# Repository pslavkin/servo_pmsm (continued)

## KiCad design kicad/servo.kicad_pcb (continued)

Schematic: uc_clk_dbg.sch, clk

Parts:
C601: 1nF; C_0603_1608Metric
C602: 0.01uF; C_0603_1608Metric
C603: 0.1uF; C_0603_1608Metric
D603: green; LED_0603_1608Metric
D604: blue; LED_0603_1608Metric
J601: dbg_conn; PinSocket_2x06_P2.54mm_Vertical
R603, R606: 1.0k; R_0603_1608Metric
R604, R605: 56k; R_0805_2012Metric_Pad1.15x1.40mm_HandSolder
R607, R610: 2.2k; R_0603_1608Metric
R608, R609: 680; R_0603_1608Metric
U301: TMS320F28388DZWTS; BGA337CP80_19X19_1600X1600X140B50N; PartNumber TMS320F28388DZWTS
U601: SN74ALVC244PW; TSSOP-20_4.4x6.5mm_P0.65mm
U602: M25PX32-VMW; SOIJ-8_5.3x5.3mm_P1.27mm
Y601: Oscillator_SMD_SeikoEpson_SG210-4Pin_2.5x2.0mm

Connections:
3V3: C603.2 (Capacitor), D603.2 (A), D604.2 (A), J601.2, R604.1, R605.1, R610.2, U601.1 (1~OE), U601.19 (2~OE), U601.20 (VCC), U602.3 (W#/VPP), U602.7 (HOLD#), U602.8 (VCC), Y601.1 (TRI-STATE), Y601.4 (VCC); also elsewhere on the board
5VC: J601.1; also elsewhere on the board
/uc_clk_dbg/F2838x_CLK: U301.G19 (X1), Y601.3 (OUTPUT)
/uc_clk_dbg/MCU_TCK: U301.V15 (TCK), U601.18 (1Y1)
/uc_clk_dbg/MCU_TDI: U301.W13 (TDI), U601.16 (1Y2)
/uc_clk_dbg/MCU_TDO: U301.W15 (TDO), U601.11 (2A1)
/uc_clk_dbg/MCU_TMS: U301.W14 (TMS), U601.14 (1Y3)
/uc_clk_dbg/MCU_TRSTn: R607.2, U301.V14 (TRST), U601.12 (1Y4)
/uc_clk_dbg/MCU_XRSn: C602.1, R610.1, U301.F19 (XRS)
/uc_clk_dbg/PRG_SCI_RX: J601.4, R603.2, U601.5 (2Y3)
/uc_clk_dbg/PRG_SCI_TX: J601.3, U601.17 (2A4)
/uc_clk_dbg/PRG_TCK: J601.12, U601.2 (1A1)
/uc_clk_dbg/PRG_TDI: J601.11, U601.4 (1A2)
/uc_clk_dbg/PRG_TDO: J601.8, U601.9 (2Y1)
/uc_clk_dbg/PRG_TMS: J601.10, U601.6 (1A3)
/uc_clk_dbg/PRG_TRSTn: J601.9, U601.8 (1A4)
BOOT1: R604.2; also elsewhere on the board
BOOT2: R605.2; also elsewhere on the board
DACB_DBG: R608.1; also elsewhere on the board
DACB_DBG_OUT: J601.7, R609.2
FLASH_SPI_CLK: U602.6 (C); also elsewhere on the board
FLASH_SPI_CS: U602.1 (S#); also elsewhere on the board
FLASH_SPI_MISO: U602.2 (DQ1); also elsewhere on the board
FLASH_SPI_MOSI: U602.5 (DQ0); also elsewhere on the board
GND: C601.1, C602.2 (Capacitor), C603.1, J601.5, J601.6, R607.1, U601.10 (GND), U601.13 (2A2), U602.4 (VSS), Y601.2 (GND); also elsewhere on the board
unnamed: C601.2 (Capacitor), R608.2, R609.1
unnamed: D603.1 (K), R603.1
unnamed: D604.1 (K), R606.1
SCIA_RX: R606.2, U601.3 (2Y4); also elsewhere on the board
SCIA_TX: U601.15 (2A3); also elsewhere on the board

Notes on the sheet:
I left fixed in flash mode if you need to change it you'll get dirty
25MHz Clock
Reset
SPI FLASH
To store some firmware features, and maybe UI images or screens
ADC/DAC DBG OUT
it's just optional for debug porpouses to monitor some analog signal out from the board, it could be very handy
Programmer connector plus SCI for debug porpouses.. take in account that it's not isolated, only buffered to minimize risk. It's supoussed that th 3v3 cold side never touch 220v
CLK + JTAG + SCI
BOOTSRAP R's

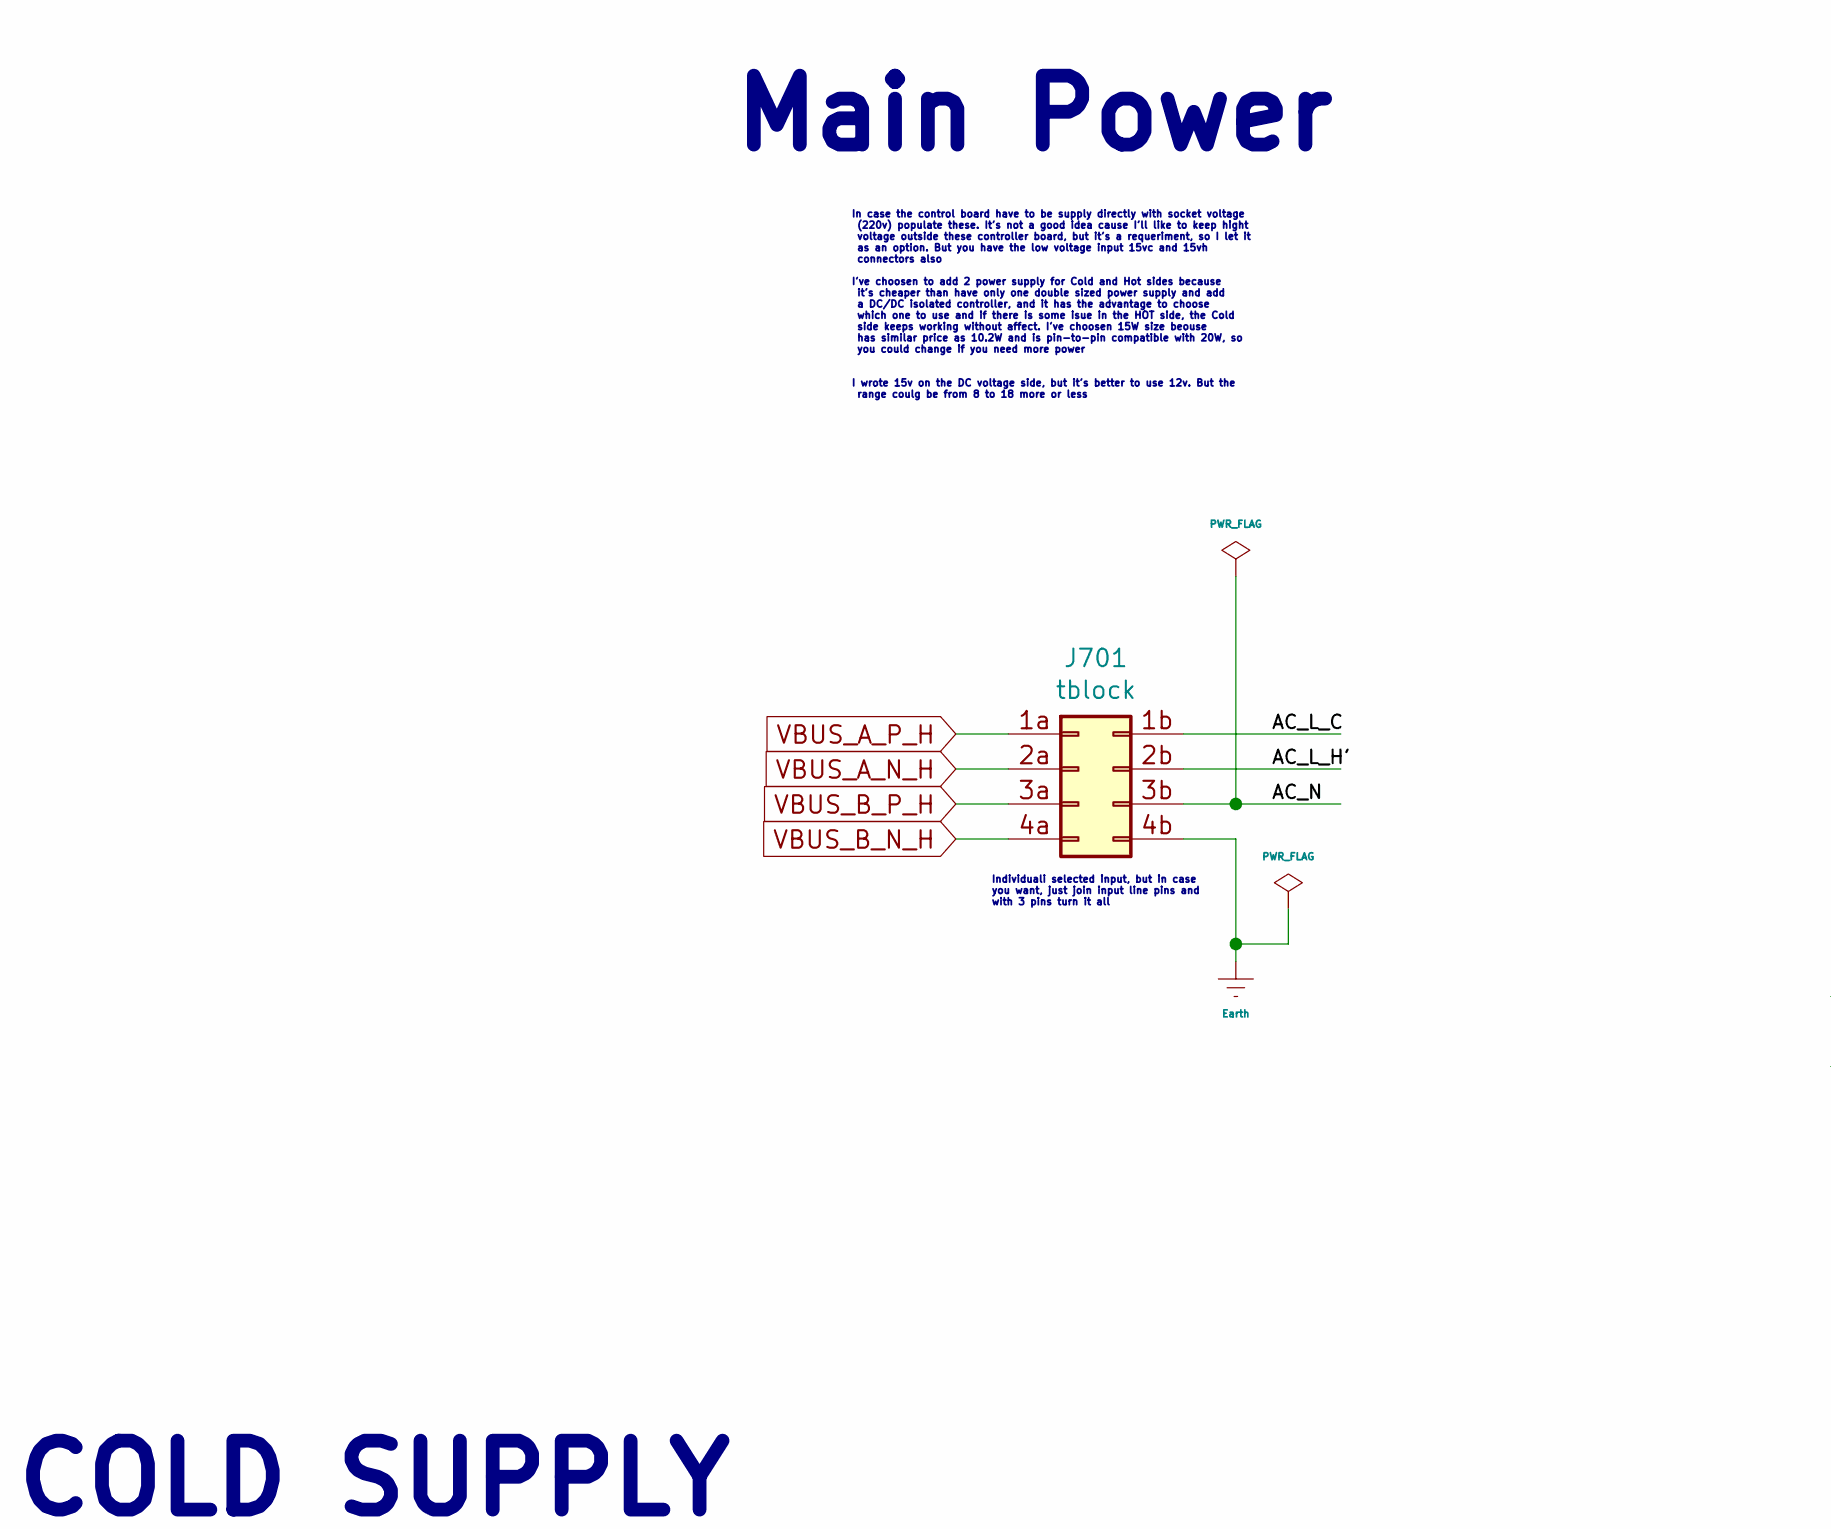
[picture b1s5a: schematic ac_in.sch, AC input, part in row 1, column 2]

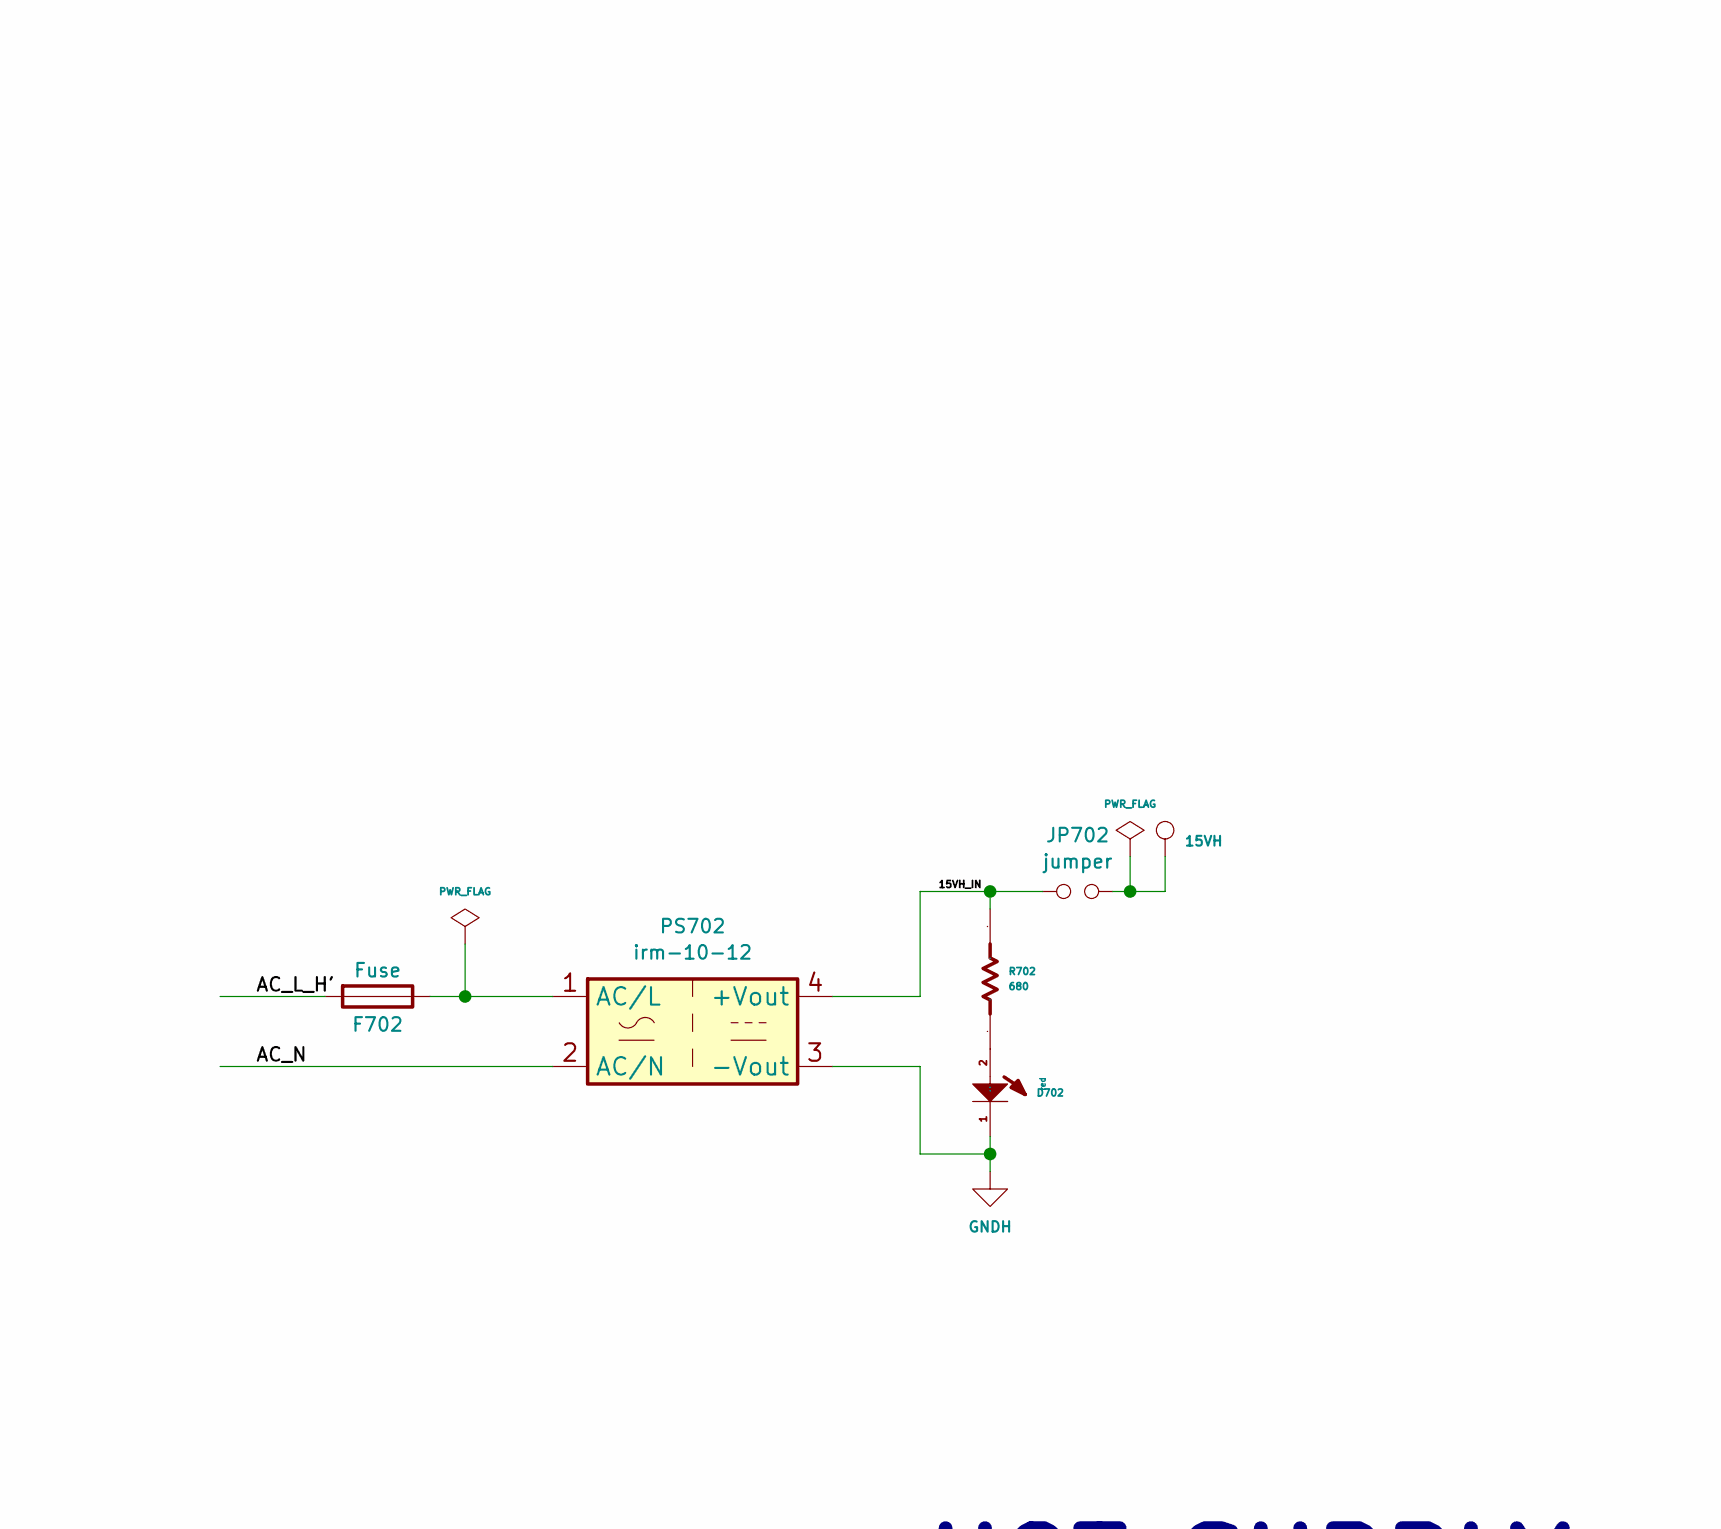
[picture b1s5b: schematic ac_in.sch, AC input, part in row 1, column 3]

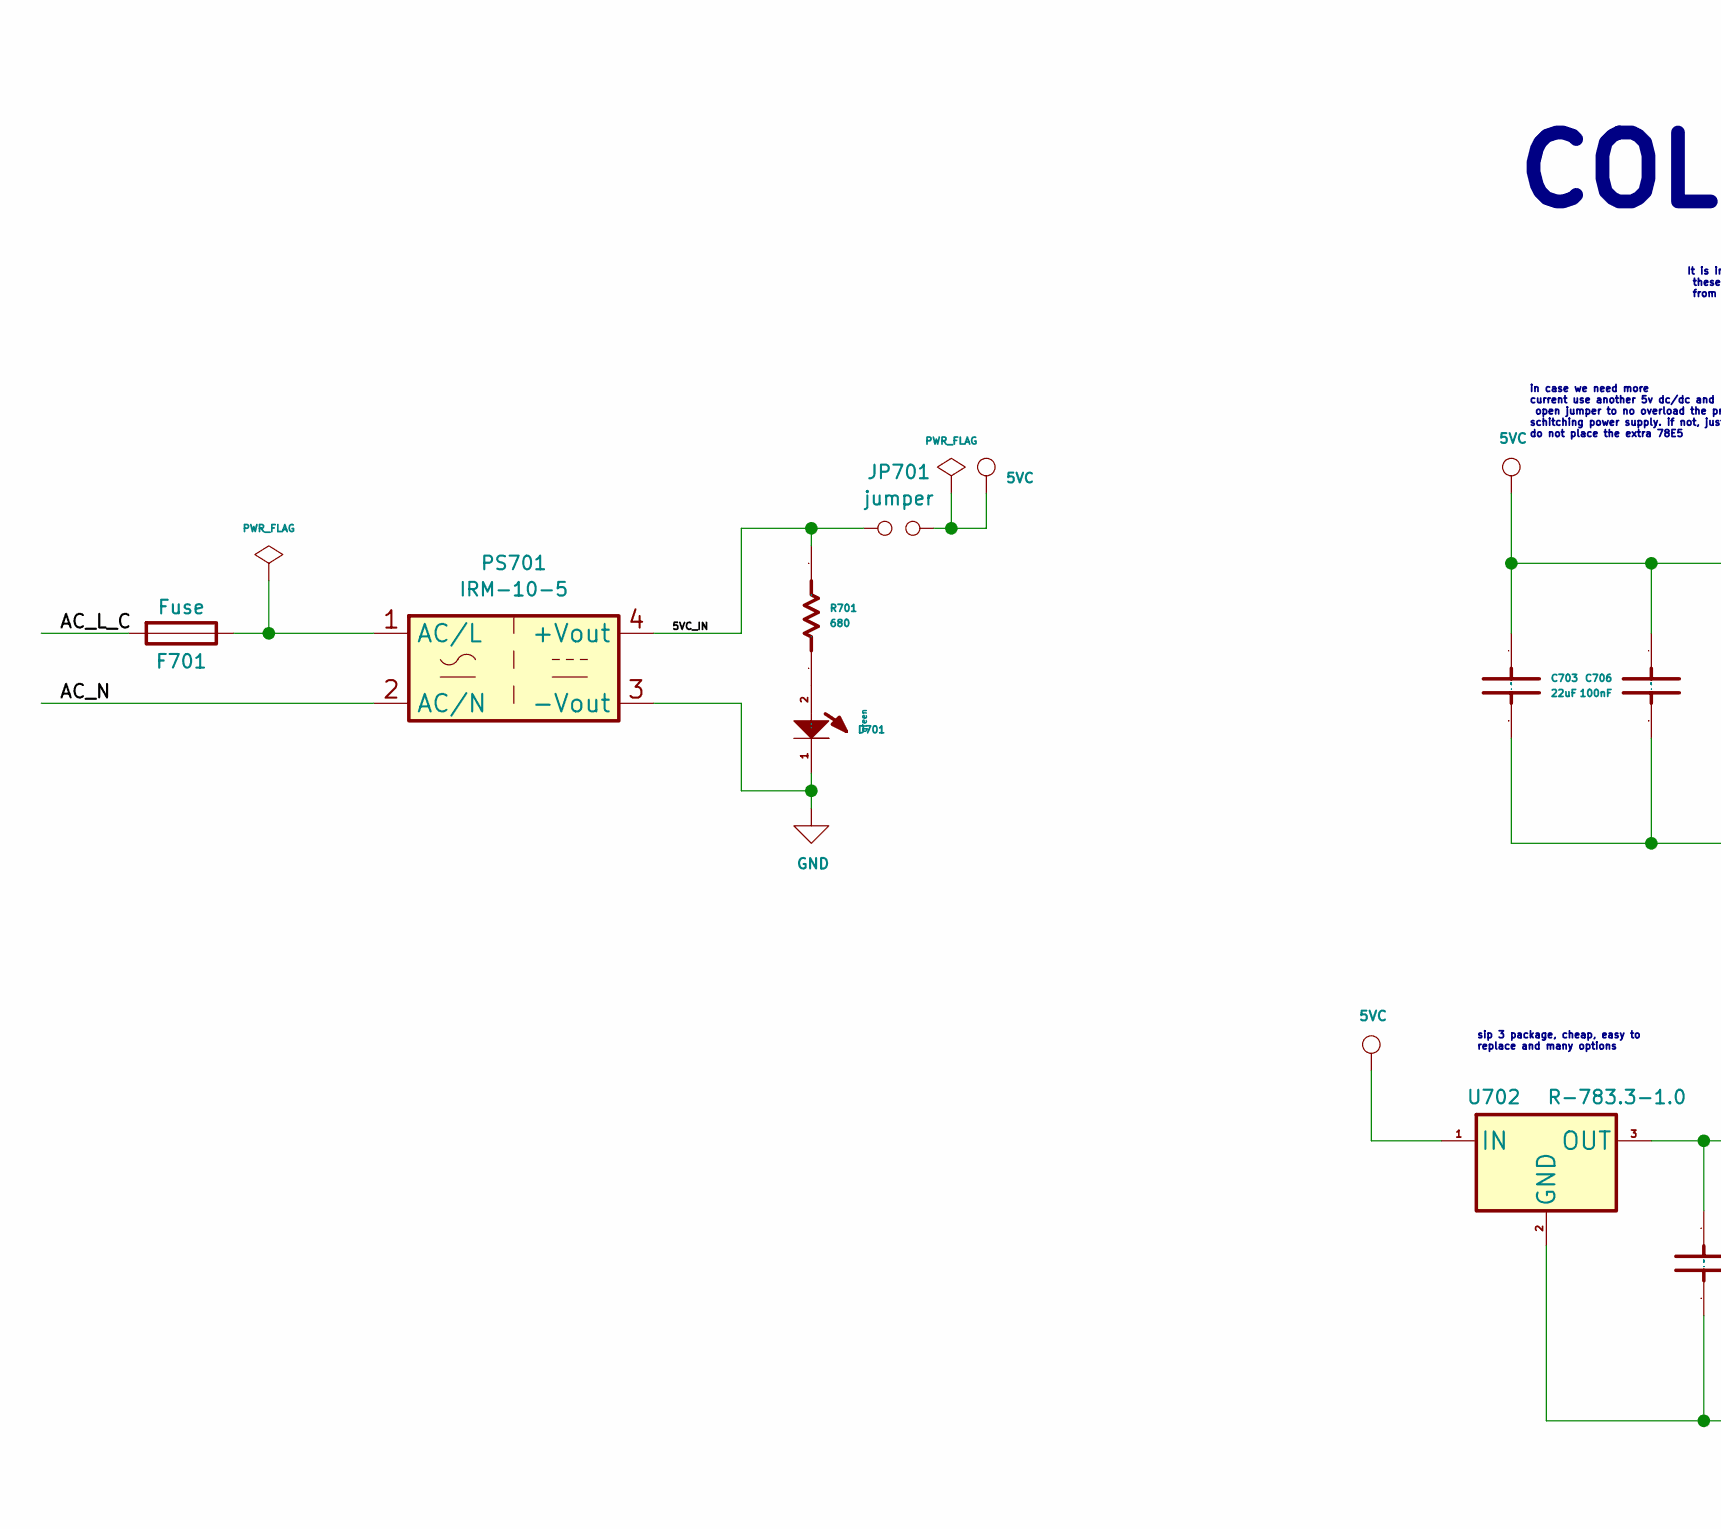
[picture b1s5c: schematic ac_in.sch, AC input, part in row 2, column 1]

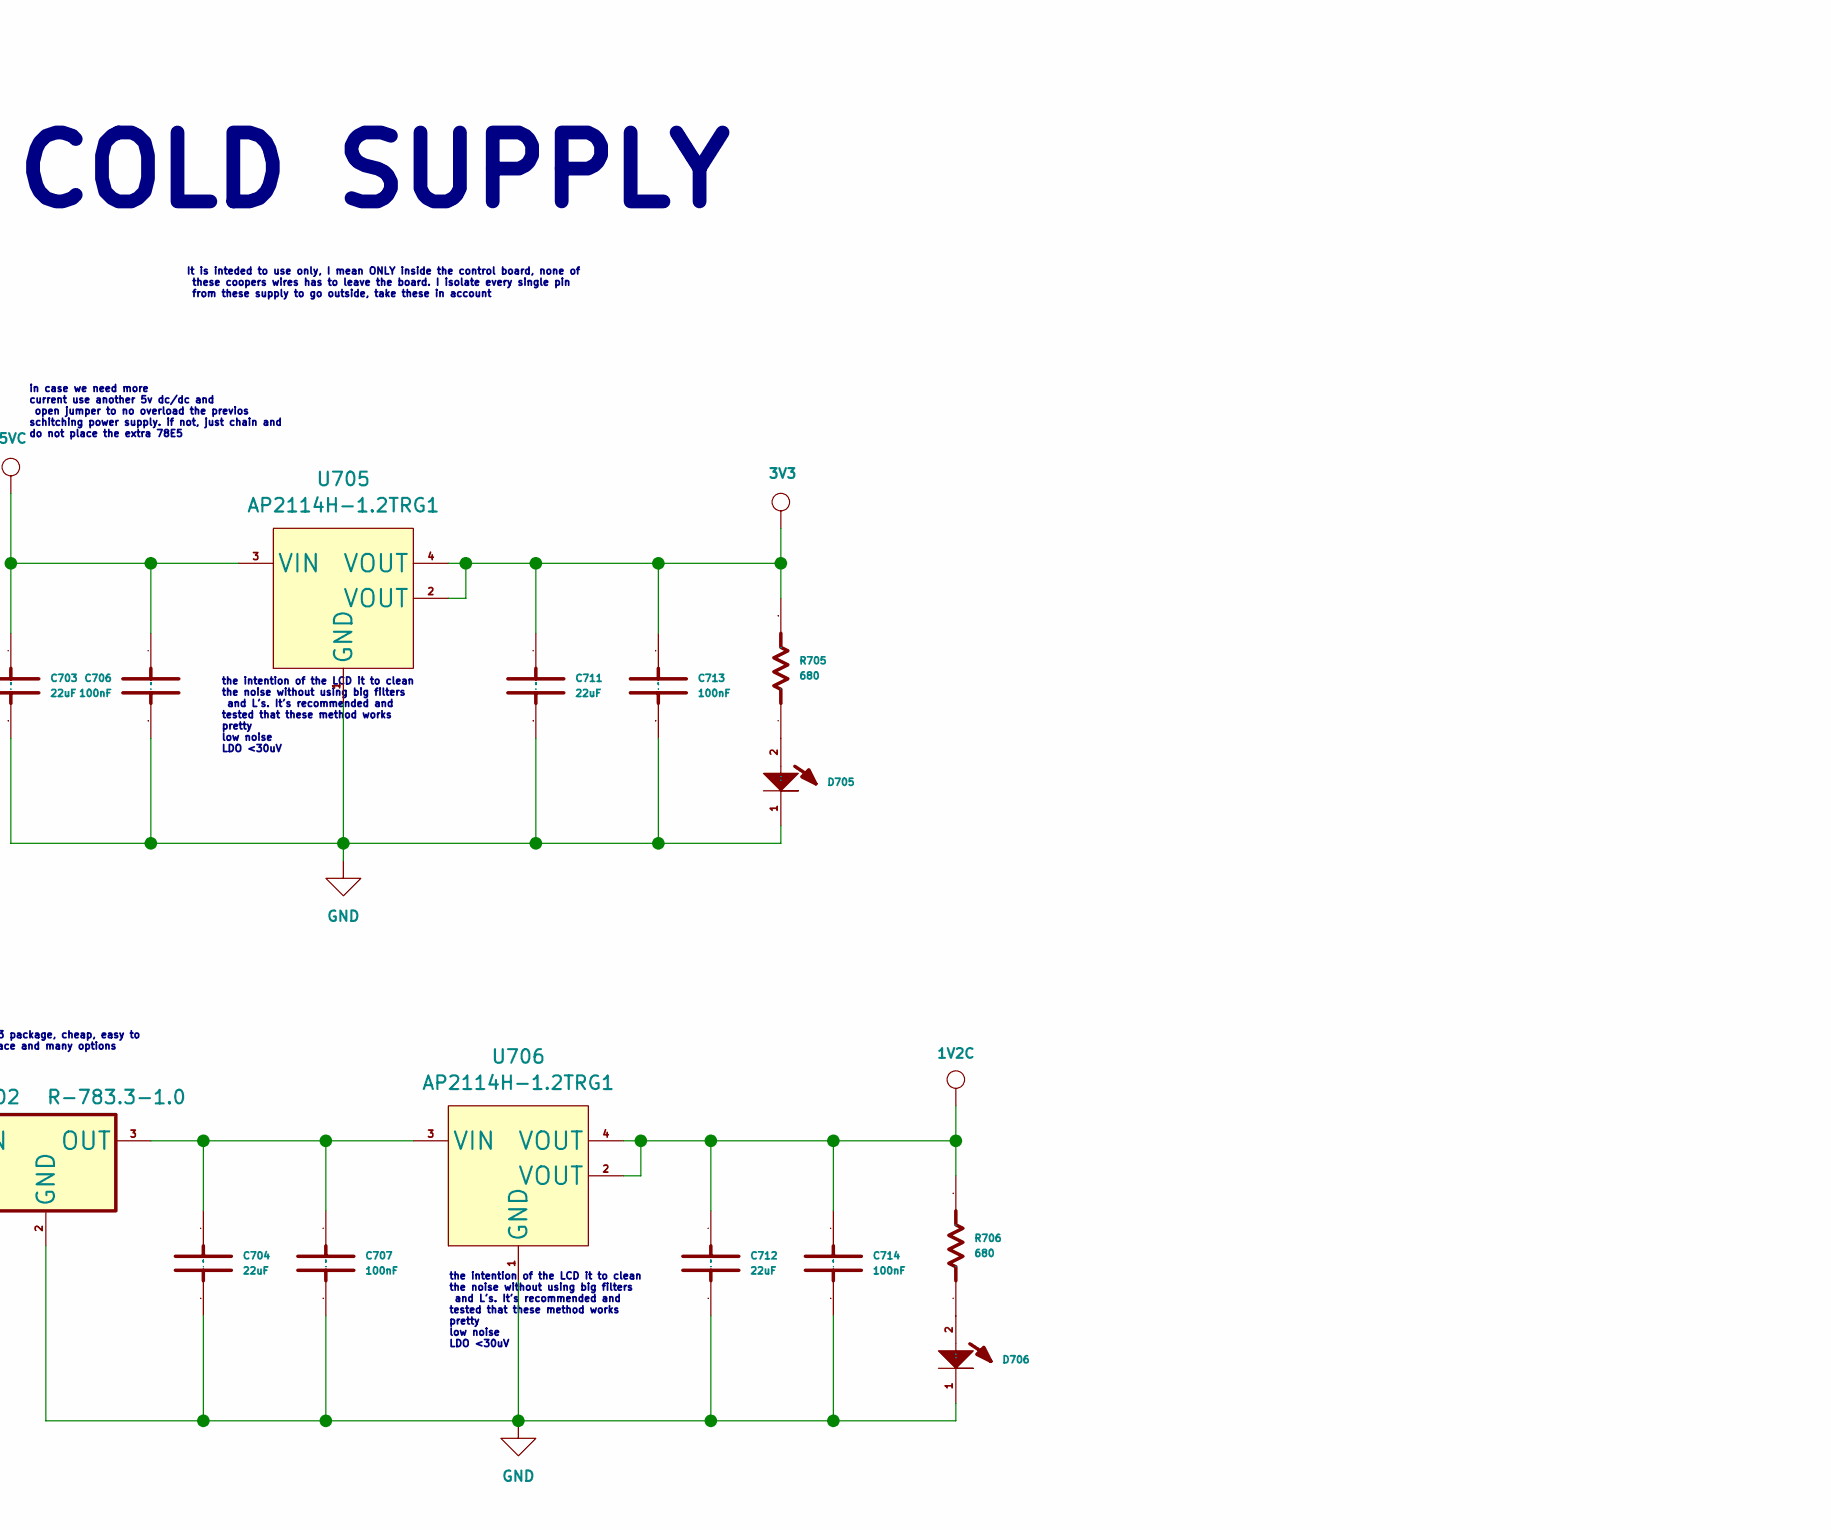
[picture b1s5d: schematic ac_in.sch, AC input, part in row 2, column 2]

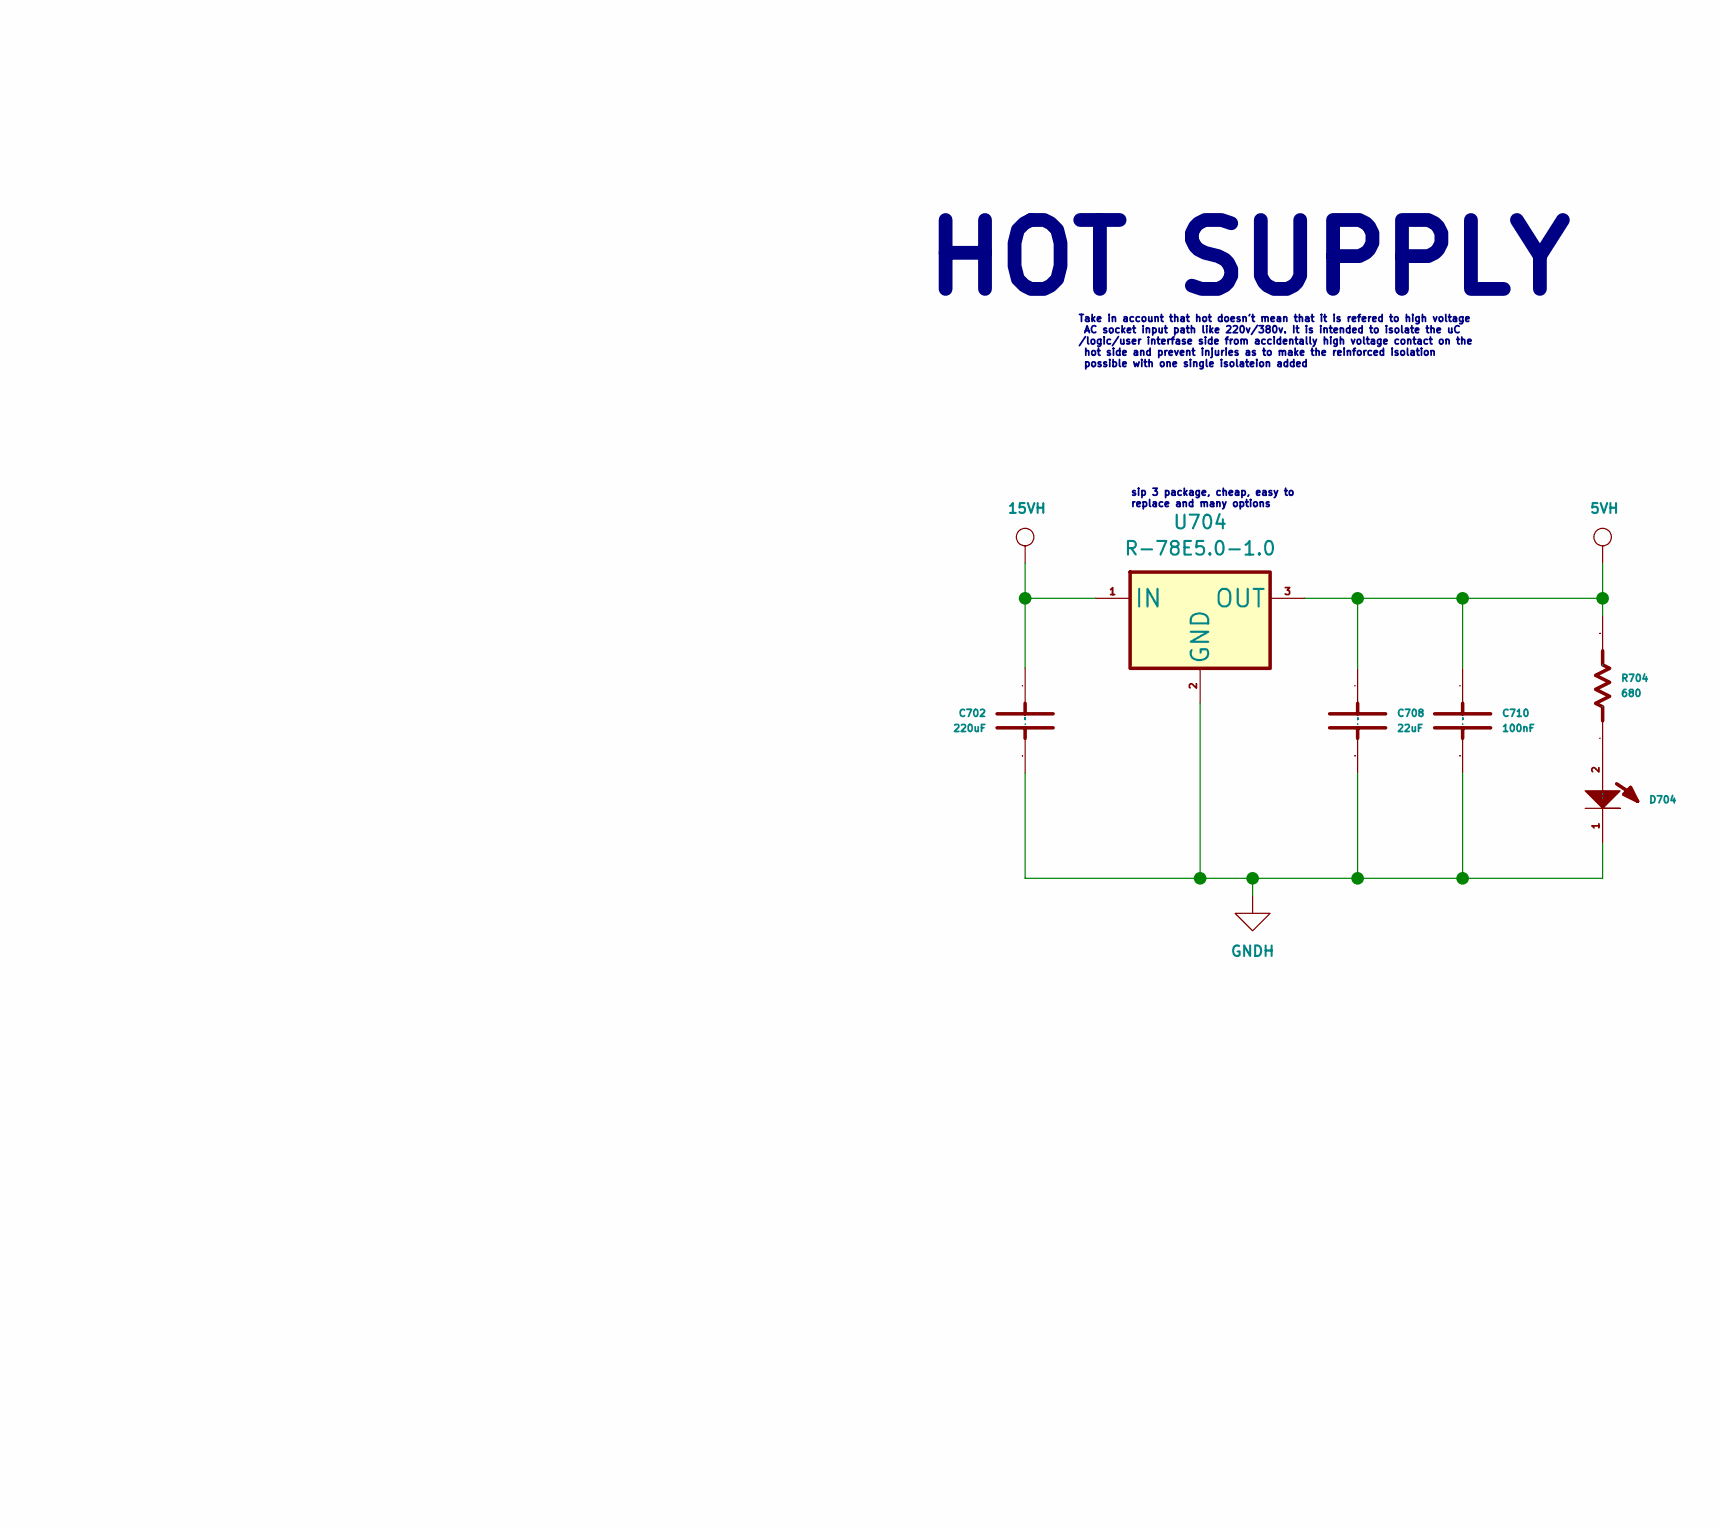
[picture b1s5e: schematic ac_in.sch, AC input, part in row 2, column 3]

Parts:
C702: 220uF; C_0603_1608Metric
C703, C704, C708, C711, C712: 22uF; C_0603_1608Metric
C706, C707, C710, C713, C714: 100nF; C_0603_1608Metric
D701, D705: green; LED_0603_1608Metric
D702, D704: red; LED_0603_1608Metric
D706: blue; LED_0603_1608Metric
F701, F702: Fuse; fuse_3912
J701: tblock; tblock02x04
JP701, JP702: jumper; SolderJumper-2_P1.3mm_Open_RoundedPad1.0x1.5mm
PS701: IRM-10-5; Converter_ACDC_MeanWell_IRM-10-xx_THT
PS702: irm-10-12; Converter_ACDC_MeanWell_IRM-10-xx_THT
R701, R702, R704, R705, R706: 680; R_0603_1608Metric
U702: R-783.3-1.0; Converter_DCDC_RECOM_R-78E-0.5_THT
U704: R-78E5.0-1.0; Converter_DCDC_RECOM_R-78E-0.5_THT
U705, U706: AP2114H-1.2TRG1; SOT-223

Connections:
1V2C: C712.2 (Capacitor), C714.2 (Capacitor), R706.1, U706.2 (VOUT), U706.4 (VOUT); also elsewhere on the board
3V3: C711.2 (Capacitor), C713.2 (Capacitor), R705.1, U705.2 (VOUT), U705.4 (VOUT); also elsewhere on the board
5VC: C703.2 (Capacitor), C706.2 (Capacitor), JP701.2, U702.1 (IN), U705.3 (VIN); also elsewhere on the board
5VH: C708.2 (Capacitor), C710.2 (Capacitor), R704.1, U704.3 (OUT); also elsewhere on the board
15VH: C702.2 (Capacitor), JP702.2, U704.1 (IN); also elsewhere on the board
/ac_in/5VC_IN: JP701.1, PS701.4 (+Vout), R701.1
/ac_in/15VH_IN: JP702.1, PS702.4 (+Vout), R702.1
/ac_in/AC_L_C: F701.2, J701.1b
/ac_in/AC_L_H': F702.2, J701.2b
/ac_in/AC_N: J701.3b, PS701.2 (AC/N), PS702.2 (AC/N)
Earth: J701.4b; also elsewhere on the board
GND: C703.1, C704.1, C706.1, C707.1, C711.1, C712.1, C713.1, C714.1, D701.1 (K), D705.1 (K), D706.1 (K), PS701.3 (-Vout), U702.2 (GND), U705.1 (GND), U706.1 (GND); also elsewhere on the board
GNDH: C702.1, C708.1, C710.1, D702.1 (K), D704.1 (K), PS702.3 (-Vout), U704.2 (GND); also elsewhere on the board
unnamed: C704.2 (Capacitor), C707.2 (Capacitor), U702.3 (OUT), U706.3 (VIN)
unnamed: D701.2 (A), R701.2
unnamed: D702.2 (A), R702.2
unnamed: D704.2 (A), R704.2
unnamed: D705.2 (A), R705.2
unnamed: D706.2 (A), R706.2
unnamed: F701.1, PS701.1 (AC/L)
unnamed: F702.1, PS702.1 (AC/L)
VBUS_A_N_H: J701.2a; also elsewhere on the board
VBUS_A_P_H: J701.1a; also elsewhere on the board
VBUS_B_N_H: J701.4a; also elsewhere on the board
VBUS_B_P_H: J701.3a; also elsewhere on the board

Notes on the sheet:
in case we need more current use another 5v dc/dc and open jumper to no overload the previos schitching power supply. if not, just chain and do not place the extra 78E5
COLD SUPPLY
HOT SUPPLY
Main Power
Take in account that hot doesn't mean that it is refered to high voltage AC socket input path like 220v/380v. It is intended to isolate the uC /logic/user interfase side from accidentally high voltage contact on the hot side and prevent injuries as to make the reinforced isolation possible with one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
sip 3 package, cheap, easy to replace and many options
In case the control board have to be supply directly with socket voltage (220v) populate these. It's not a good idea cause I'll like to keep hight voltage outside these controller board, but it's a requeriment, so I let it as an option. But you have the low voltage input 15vc and 15vh connectors al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
It is inteded to use only, I mean ONLY inside the control board, none of these coopers wires has to leave the board. I isolate every single pin from these supply to go outside, take these in account
the intention of the LCD it to clean the noise without using big filters and L's. It's recommended and tested that these method works pretty low noise LDO <30uV
Individuali selected input, but in case you want, just join input line pins and with 3 pins turn it all
